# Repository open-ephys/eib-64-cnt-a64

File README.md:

# EIB for CNT A64 probes

- 64 electrodes
- Power ground (GND), amplifier reference (REF), VCoax, LED Cathode 0 and 1, and I-stim signals exposed via 2.54mm header
- Compatible with:
  - [Low Profile SPI](https://open-ephys.org/acquisition-system/oeps-6570-6571)
  - [headstage-64](https://open-ephys.org/onix/oeps-7741)

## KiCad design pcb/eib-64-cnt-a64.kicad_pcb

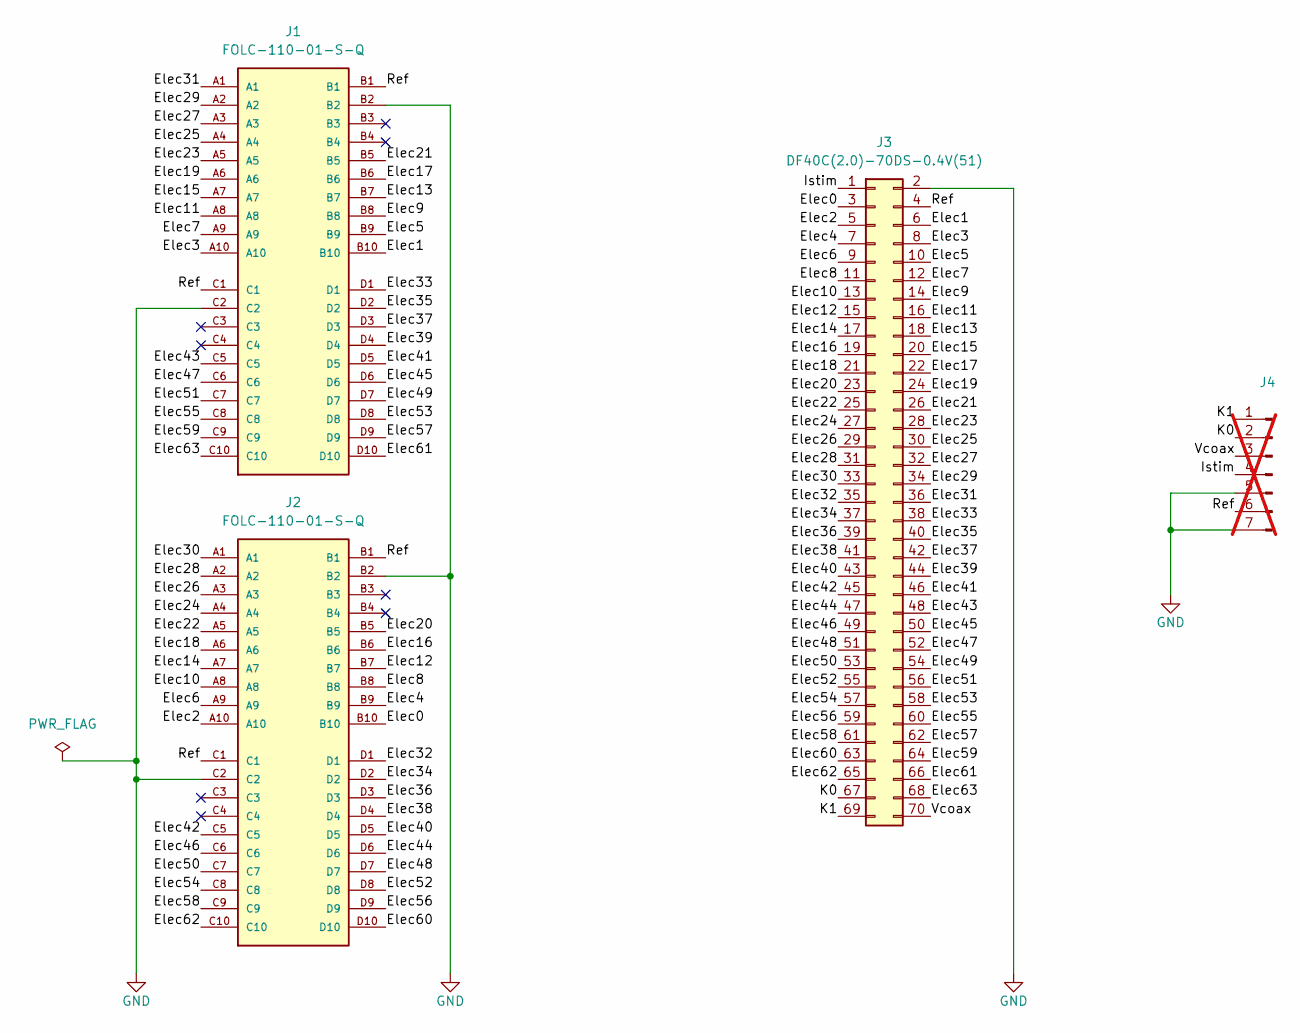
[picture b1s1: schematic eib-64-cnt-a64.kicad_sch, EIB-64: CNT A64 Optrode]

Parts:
J1, J2: FOLC-110-01-S-Q; SAMTEC_FOLC-110-01-S-Q
J3: DF40C(2.0)-70DS-0.4V(51); HIROSE_DF40C(2.0)-70DS-0.4V(51)
J4: Conn_01x07_Male; PinHeader_1x07_P2.54mm_Vertical; not fitted

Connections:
/Elec0: J2.B10, J3.3
/Elec1: J1.B10, J3.6
/Elec2: J2.A10, J3.5
/Elec3: J1.A10, J3.8
/Elec4: J2.B9, J3.7
/Elec5: J1.B9, J3.10
/Elec6: J2.A9, J3.9
/Elec7: J1.A9, J3.12
/Elec8: J2.B8, J3.11
/Elec9: J1.B8, J3.14
/Elec10: J2.A8, J3.13
/Elec11: J1.A8, J3.16
/Elec12: J2.B7, J3.15
/Elec13: J1.B7, J3.18
/Elec14: J2.A7, J3.17
/Elec15: J1.A7, J3.20
/Elec16: J2.B6, J3.19
/Elec17: J1.B6, J3.22
/Elec18: J2.A6, J3.21
/Elec19: J1.A6, J3.24
/Elec20: J2.B5, J3.23
/Elec21: J1.B5, J3.26
/Elec22: J2.A5, J3.25
/Elec23: J1.A5, J3.28
/Elec24: J2.A4, J3.27
/Elec25: J1.A4, J3.30
/Elec26: J2.A3, J3.29
/Elec27: J1.A3, J3.32
/Elec28: J2.A2, J3.31
/Elec29: J1.A2, J3.34
/Elec30: J2.A1, J3.33
/Elec31: J1.A1, J3.36
/Elec32: J2.D1, J3.35
/Elec33: J1.D1, J3.38
/Elec34: J2.D2, J3.37
/Elec35: J1.D2, J3.40
/Elec36: J2.D3, J3.39
/Elec37: J1.D3, J3.42
/Elec38: J2.D4, J3.41
/Elec39: J1.D4, J3.44
/Elec40: J2.D5, J3.43
/Elec41: J1.D5, J3.46
/Elec42: J2.C5, J3.45
/Elec43: J1.C5, J3.48
/Elec44: J2.D6, J3.47
/Elec45: J1.D6, J3.50
/Elec46: J2.C6, J3.49
/Elec47: J1.C6, J3.52
/Elec48: J2.D7, J3.51
/Elec49: J1.D7, J3.54
/Elec50: J2.C7, J3.53
/Elec51: J1.C7, J3.56
/Elec52: J2.D8, J3.55
/Elec53: J1.D8, J3.58
/Elec54: J2.C8, J3.57
/Elec55: J1.C8, J3.60
/Elec56: J2.D9, J3.59
/Elec57: J1.D9, J3.62
/Elec58: J2.C9, J3.61
/Elec59: J1.C9, J3.64
/Elec60: J2.D10, J3.63
/Elec61: J1.D10, J3.66
/Elec62: J2.C10, J3.65
/Elec63: J1.C10, J3.68
/Istim: J3.1, J4.4
/K0: J3.67, J4.2
/K1: J3.69, J4.1
/Ref: J1.B1, J1.C1, J2.B1, J2.C1, J3.4, J4.6
/Vcoax: J3.70, J4.3
GND: J1.B2, J1.C2, J2.B2, J2.C2, J3.2, J4.5, J4.7

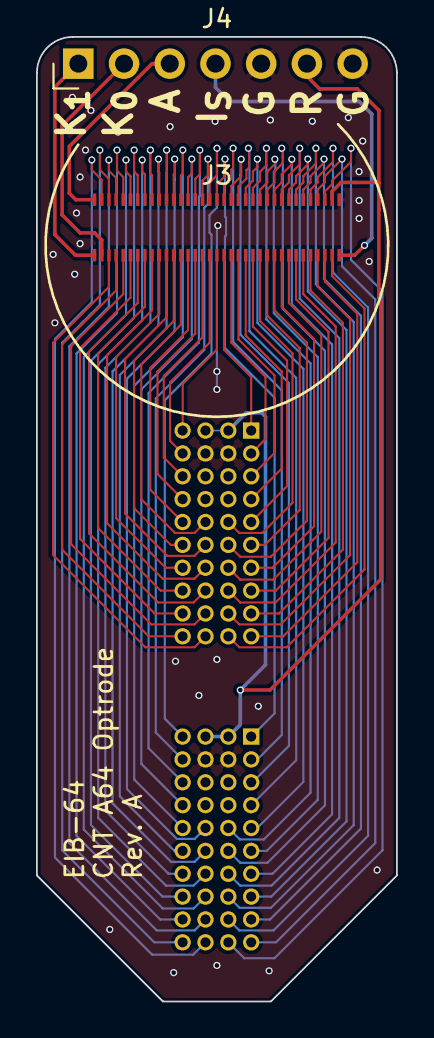
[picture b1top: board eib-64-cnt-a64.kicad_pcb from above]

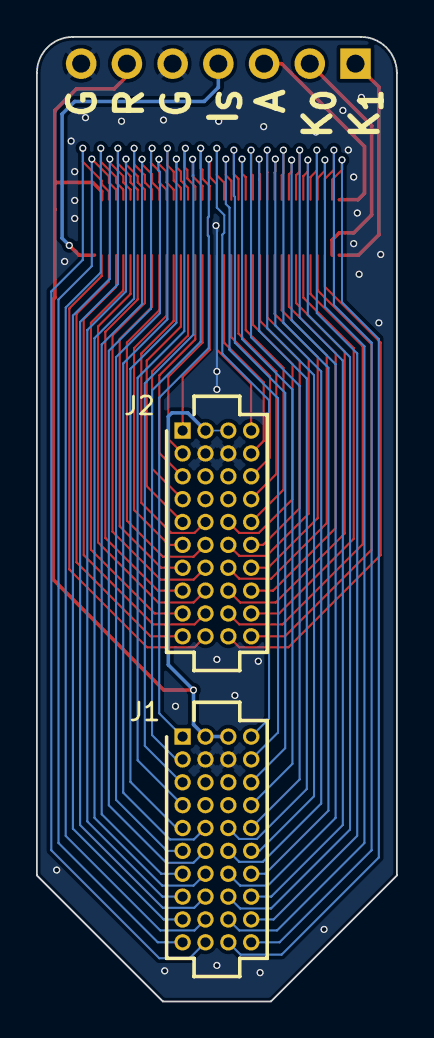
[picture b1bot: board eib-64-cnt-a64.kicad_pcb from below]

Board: 4 copper layers, 20.0 x 53.6 mm, 4 parts (2 on the bottom side), 70 nets.

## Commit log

2025-09-24 Initial commit
    - Rev. A inital design
2025-09-30 Revision A
    - Set to JLC for production
2025-10-23 Revision A
    - This was fabricated and tested.
